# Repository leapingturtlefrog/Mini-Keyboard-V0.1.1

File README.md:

# Mini Keyboard V0.1.1
Made using [atopile](atopile.io)
<br>

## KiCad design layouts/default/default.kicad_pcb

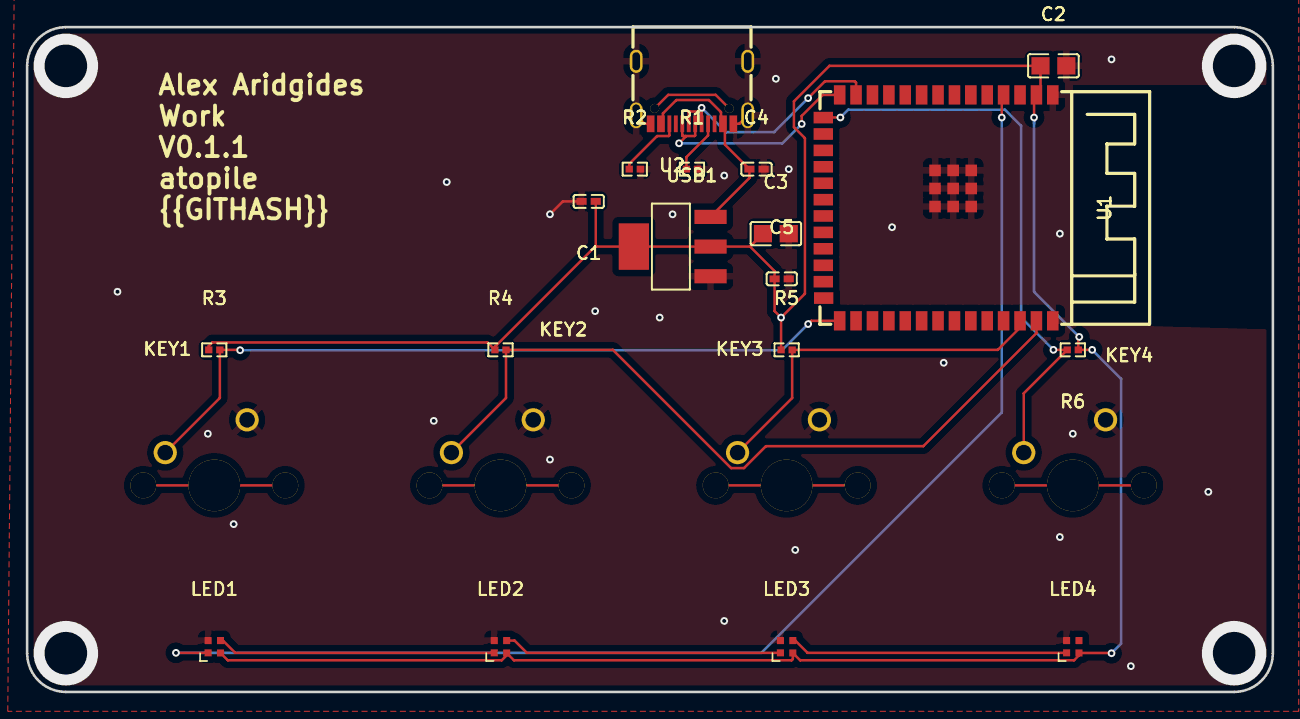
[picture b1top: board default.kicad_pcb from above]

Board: 2 copper layers, 96.5 x 51.5 mm, 22 parts (0 on the bottom side), 15 nets.

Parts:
C1: 100nF ±10% 16V X7R; C0402
C2, C3: 10nF ±10% 50V X7R; C0805
C4, C5: 1µF ±10% 25V X5R; C0402
KEY1, KEY2, KEY3, KEY4: KEY-TH_28115181DM
LED1, LED2, LED3, LED4: LED-SMD_4P-L1.5-W1.5-BL
R1, R2: 5.1kΩ ±1% 62.5mW; R0402
R3, R4, R5, R6: 10kΩ ±1% 62.5mW; R0402
U1: WIRELM-SMD_ESP32-S3-WROOM-1
U2: SOT-223-3_L6.5-W3.4-P2.30-LS7.0-BR
USB1: USB-C-SMD_KH-TYPE-C-16P

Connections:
A5: R1.1, USB1.A5
A7: U1.13, USB1.A7, USB1.B7
CC2: R2.1, USB1.B5
DP2: U1.14, USB1.A6, USB1.B6
gnd: C1.2, C2.2, C3.2, C4.2, C5.2, KEY1.2, KEY2.2, KEY3.2, KEY4.2, LED1.4, LED2.4, LED3.4, LED4.4, R1.2, R2.2, U1.1, U1.40, U1.41, U2.1, USB1.1, USB1.2, USB1.3, USB1.4, USB1.A1, USB1.A12, USB1.B1, USB1.B12
hid_controller-DIN: LED1.3, LED2.1
hid_controller-DIN-1: LED2.3, LED3.1
hid_controller-DIN-2: LED3.3, LED4.1
hid_controller-DIN-3: LED1.1, U1.4
hid_controller-hv: C1.1, C2.1, C3.1, C5.1, LED1.2, LED2.2, LED3.2, LED4.2, R3.1, R4.1, R5.1, R6.1, U1.2, U2.2, U2.4
hid_controller-hv-1: C4.1, U2.3, USB1.A4, USB1.A9, USB1.B4, USB1.B9
hid_controller-line: KEY3.1, R5.2, U1.38
hid_controller-line-1: KEY4.1, R6.2, U1.15
hid_controller-line-2: KEY2.1, R4.2, U1.39
hid_controller-line-3: KEY1.1, R3.2, U1.27

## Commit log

2025-06-18 ready for shipment?
2025-06-18 upload parts
2025-06-18 update final pcb
2025-06-19 add image
